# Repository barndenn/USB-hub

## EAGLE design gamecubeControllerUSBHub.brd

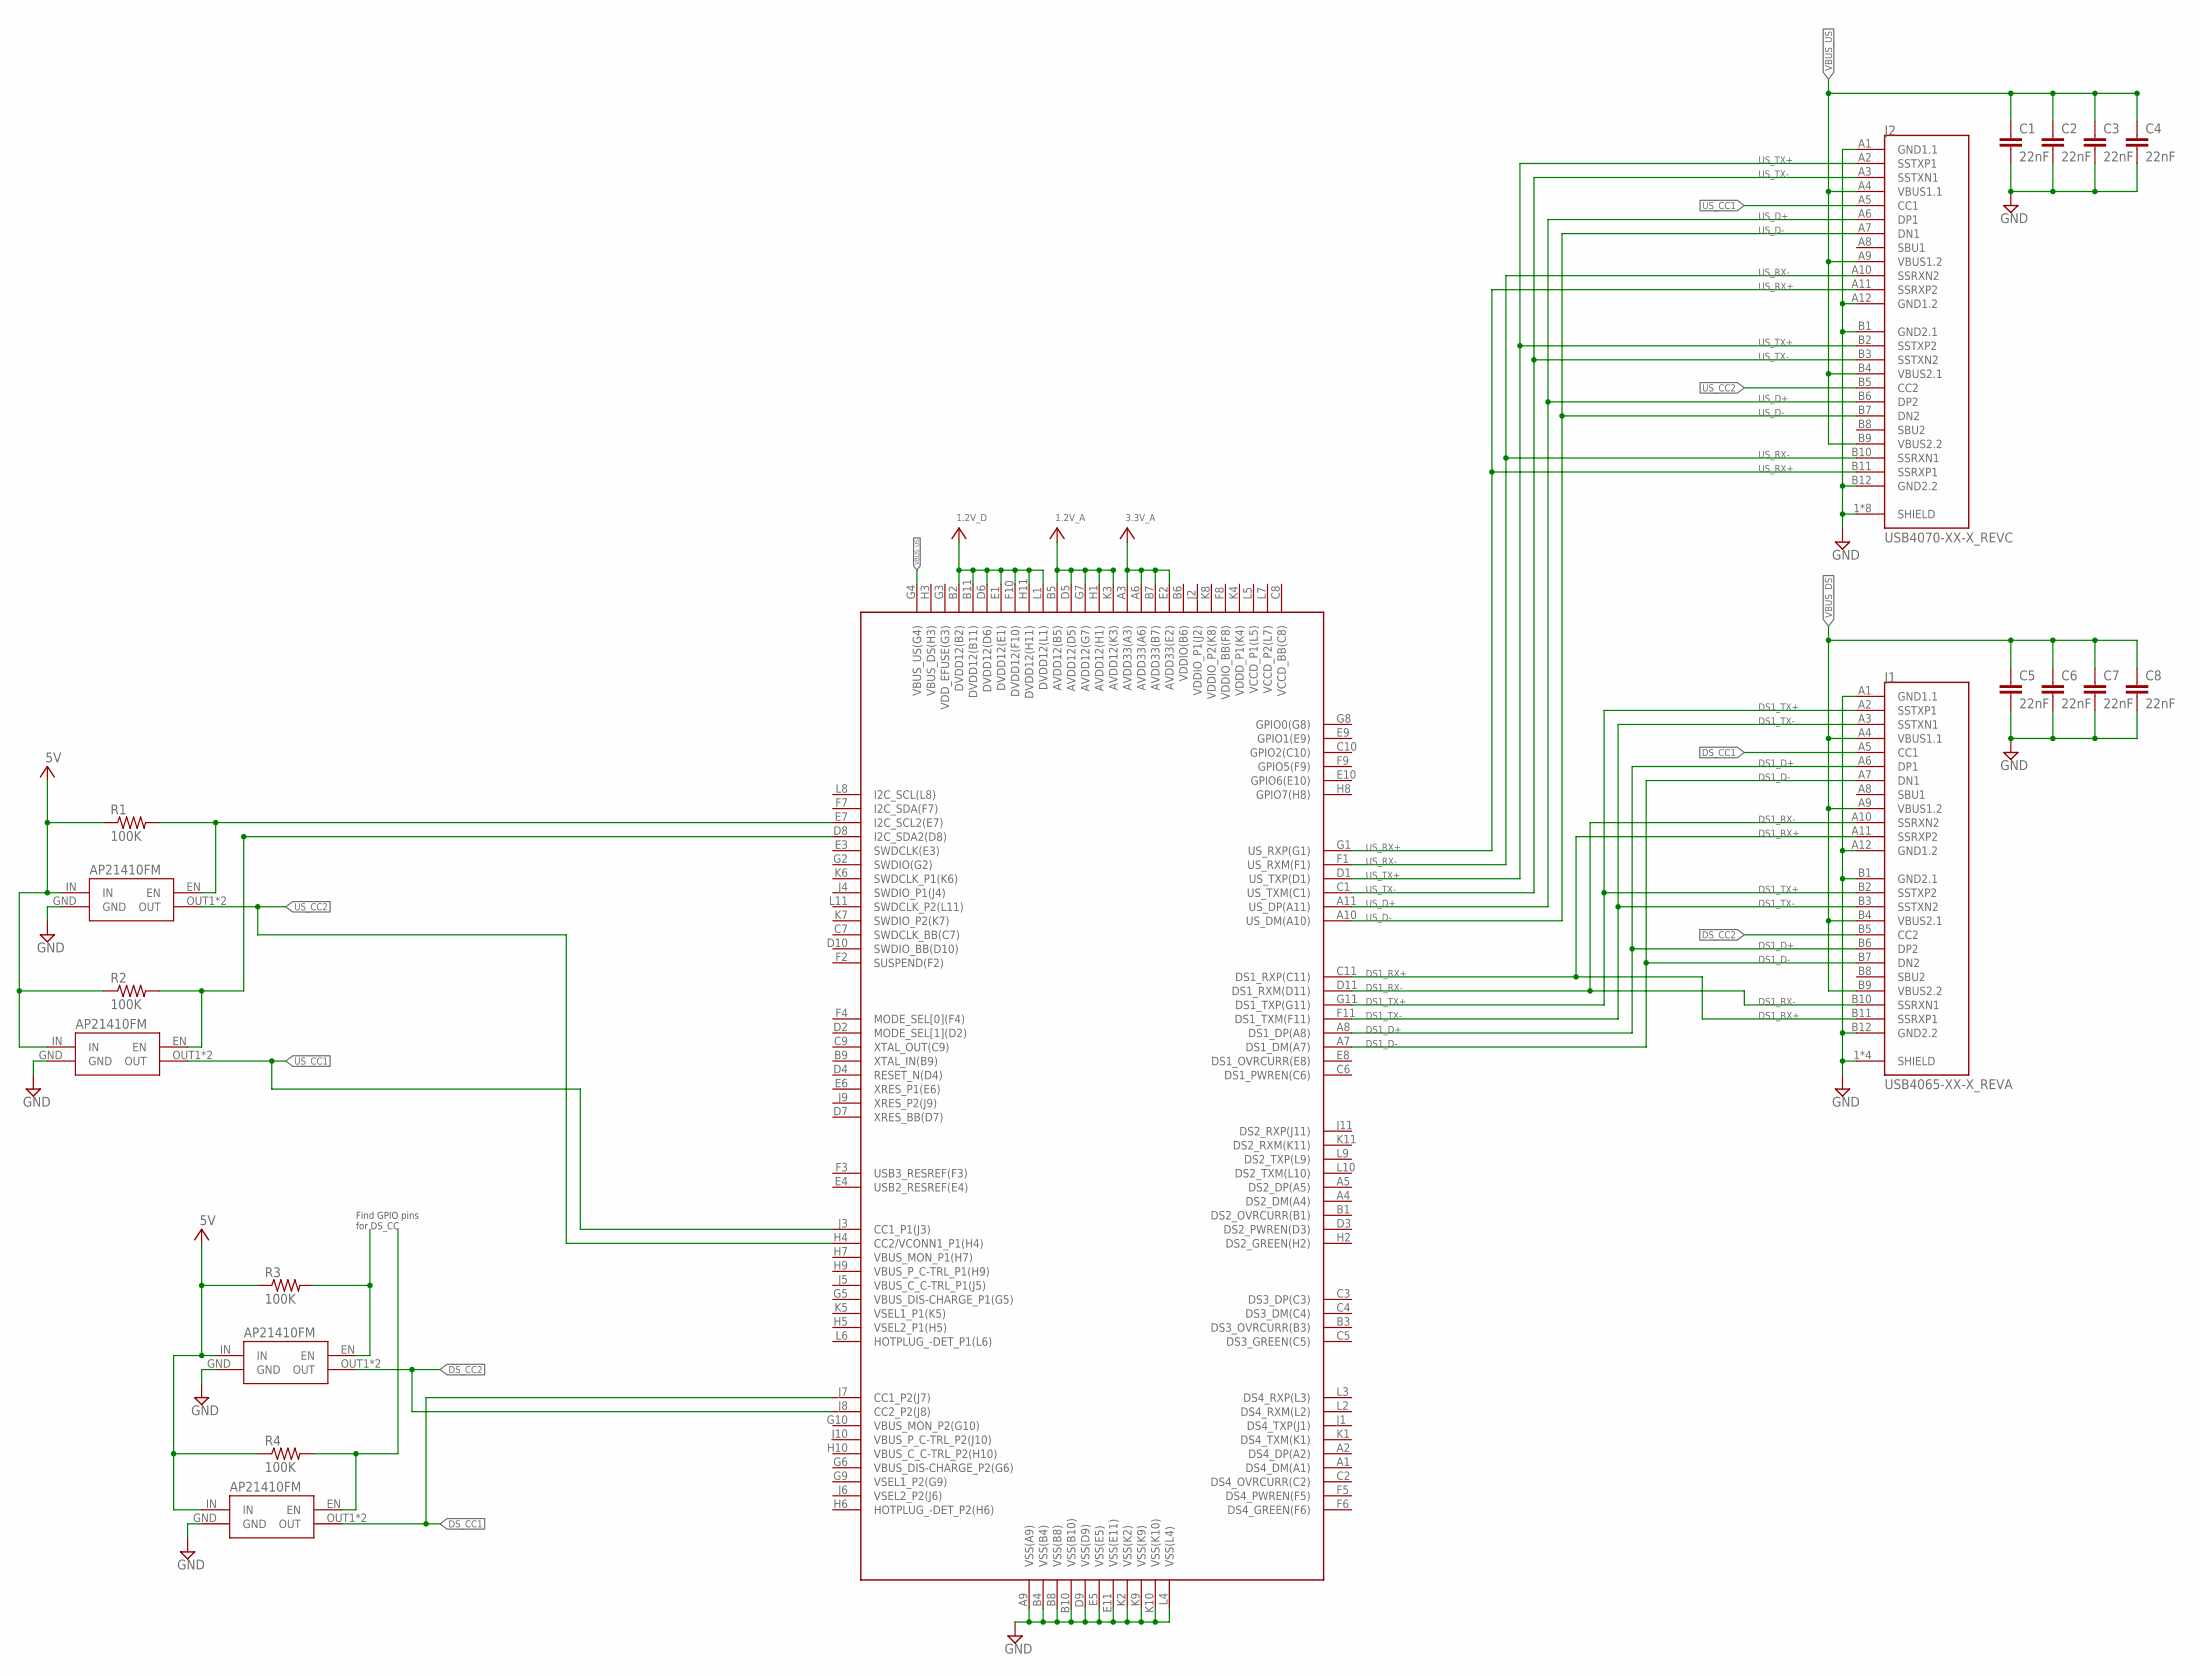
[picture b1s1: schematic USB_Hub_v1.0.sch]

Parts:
C1, C2, C3, C4, C5, C6, C7, C8: 22nF; 0603
J1: USB4065-XX-X_REVA; GCT_USB4065-XX-X_REVA
J2: USB4070-XX-X_REVC; GCT_USB4070-XX-X_REVC
R1, R2, R3, R4: 100K; R0603
U$1: CYUSB33X3
U$2, U$3, U$4, U$5: AP21410

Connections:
1.2V_A: U$1.B5 (AVDD12(B5)), U$1.D5 (AVDD12(D5)), U$1.G7 (AVDD12(G7)), U$1.H1 (AVDD12(H1)), U$1.K3 (AVDD12(K3))
1.2V_D: U$1.B2 (DVDD12(B2)), U$1.B11 (DVDD12(B11)), U$1.D6 (DVDD12(D6)), U$1.E1 (DVDD12(E1)), U$1.F10 (DVDD12(F10)), U$1.H11 (DVDD12(H11)), U$1.L1 (DVDD12(L1))
3.3V_A: U$1.A3 (AVDD33(A3)), U$1.A6 (AVDD33(A6)), U$1.B7 (AVDD33(B7)), U$1.E2 (AVDD33(E2))
5V: R1.1, R2.1, R3.1, R4.1, U$2.IN, U$3.IN, U$4.IN, U$5.IN
DS1_D+: J1.A6 (DP1), J1.B6 (DP2), U$1.A8 (DS1_DP(A8))
DS1_D-: J1.A7 (DN1), J1.B7 (DN2), U$1.A7 (DS1_DM(A7))
DS1_RX+: J1.A11 (SSRXP2), J1.B11 (SSRXP1), U$1.C11 (DS1_RXP(C11))
DS1_RX-: J1.A10 (SSRXN2), J1.B10 (SSRXN1), U$1.D11 (DS1_RXM(D11))
DS1_TX+: J1.A2 (SSTXP1), J1.B2 (SSTXP2), U$1.G11 (DS1_TXP(G11))
DS1_TX-: J1.A3 (SSTXN1), J1.B3 (SSTXN2), U$1.F11 (DS1_TXM(F11))
DS_CC1: J1.A5 (CC1), U$1.J7 (CC1_P2(J7)), U$5.OUT1 (OUT), U$5.OUT2 (OUT)
DS_CC2: J1.B5 (CC2), U$1.J8 (CC2_P2(J8)), U$4.OUT1 (OUT), U$4.OUT2 (OUT)
GND: C1.2, C2.2, C3.2, C4.2, C5.2, C6.2, C7.2, C8.2, J1.1 (SHIELD), J1.2 (SHIELD), J1.3 (SHIELD), J1.4 (SHIELD), J1.A1 (GND1.1), J1.A12 (GND1.2), J1.B1 (GND2.1), J1.B12 (GND2.2), J2.1 (SHIELD), J2.2 (SHIELD), J2.3 (SHIELD), J2.4 (SHIELD), J2.5 (SHIELD), J2.6 (SHIELD), J2.7 (SHIELD), J2.8 (SHIELD), J2.A1 (GND1.1), J2.A12 (GND1.2), J2.B1 (GND2.1), J2.B12 (GND2.2), U$1.A9 (VSS(A9)), U$1.B4 (VSS(B4)), U$1.B8 (VSS(B8)), U$1.B10 (VSS(B10)), U$1.D9 (VSS(D9)), U$1.E5 (VSS(E5)), U$1.E11 (VSS(E11)), U$1.K2 (VSS(K2)), U$1.K9 (VSS(K9)), U$1.K10 (VSS(K10)), U$1.L4 (VSS(L4)), U$2.GND, U$3.GND, U$4.GND, U$5.GND
unnamed: R1.2, U$1.E7 (I2C_SCL2(E7)), U$2.EN
unnamed: R2.2, U$1.D8 (I2C_SDA2(D8)), U$3.EN
unnamed: R3.2, U$4.EN
unnamed: R4.2, U$5.EN
US_CC1: J2.A5 (CC1), U$1.J3 (CC1_P1(J3)), U$3.OUT1 (OUT), U$3.OUT2 (OUT)
US_CC2: J2.B5 (CC2), U$1.H4 (CC2/VCONN1_P1(H4)), U$2.OUT1 (OUT), U$2.OUT2 (OUT)
US_D+: J2.A6 (DP1), J2.B6 (DP2), U$1.A11 (US_DP(A11))
US_D-: J2.A7 (DN1), J2.B7 (DN2), U$1.A10 (US_DM(A10))
US_RX+: J2.A11 (SSRXP2), J2.B11 (SSRXP1), U$1.G1 (US_RXP(G1))
US_RX-: J2.A10 (SSRXN2), J2.B10 (SSRXN1), U$1.F1 (US_RXM(F1))
US_TX+: J2.A2 (SSTXP1), J2.B2 (SSTXP2), U$1.D1 (US_TXP(D1))
US_TX-: J2.A3 (SSTXN1), J2.B3 (SSTXN2), U$1.C1 (US_TXM(C1))
VBUS_DS: C5.1, C6.1, C7.1, C8.1, J1.A4 (VBUS1.1), J1.A9 (VBUS1.2), J1.B4 (VBUS2.1), J1.B9 (VBUS2.2)
VBUS_US: C1.1, C2.1, C3.1, C4.1, J2.A4 (VBUS1.1), J2.A9 (VBUS1.2), J2.B4 (VBUS2.1), J2.B9 (VBUS2.2), U$1.G4 (VBUS_US(G4))

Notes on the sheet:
Find GPIO pins for DS_CC

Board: 2 copper layers, 19 parts (0 on the bottom side), 27 nets, no tracks yet.

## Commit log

2019-11-18 First upload
2019-11-18 Added SamacSys library
2019-11-18 Changed file names

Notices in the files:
parts and their libraries:
SparkFun-Capacitors: Licensing: Creative Commons ShareAlike 4.0 International - https://creativecommons.org/licenses/by-sa/4.0
